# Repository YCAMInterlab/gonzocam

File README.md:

# gonzocam

Open source hardware kit for disposable camera or iPhone to take pictures of wild animals automatically.

gonzocam（ゴンゾカム）は市販のインスタントカメラを使って人間含む野生動物を自動撮影するためのオープンソースハードウェアキットです。インスタントカメラに装着することで、周囲の物体の動きや加速度の変化などをトリガーにシャッターを切り、自動的にフィルムを巻き上げるなどカメラ本来の機能を拡張することができます。

詳しい情報は[YCAM Interlab | gonzocam](http://interlab.ycam.jp/projects/gonzocam)を参照してください。

## Licenses

### Hardware of gonzocam

<br />
<span xmlns:dct="http://purl.org/dc/terms/" property="dct:title">Circuit diagram, Parts list, Gerber format data</span> by <a xmlns:cc="http://creativecommons.org/ns#" href="http://yang02.org/" property="cc:attributionName" rel="cc:attributionURL">yang02</a> is licensed under a <a rel="license" href="http://creativecommons.org/licenses/by-sa/3.0/deed.en_US">Creative Commons Attribution-ShareAlike 3.0 Unported License</a>.

### Software of gonzocam

Arduino sketch by Takahiro Yamaguchi is licensed under the [Apache License, Version2.0](http://www.apache.org/licenses/LICENSE-2.0.html)

    Copyright 2013 Takahiro Yamaguchi

    Licensed under the Apache License, Version 2.0 (the "License");
    you may not use this file except in compliance with the License.
    You may obtain a copy of the License at

       http://www.apache.org/licenses/LICENSE-2.0

    Unless required by applicable law or agreed to in writing, software
    distributed under the License is distributed on an "AS IS" BASIS,
    WITHOUT WARRANTIES OR CONDITIONS OF ANY KIND, either express or implied.
    See the License for the specific language governing permissions and
    limitations under the License.

### Hardware of igonzocam

<br />
<span xmlns:dct="http://purl.org/dc/terms/" property="dct:title">Circuit diagram, Parts list</span> by <a xmlns:cc="http://creativecommons.org/ns#" href="http://www.inafact.net/" property="cc:attributionName" rel="cc:attributionURL">inafact</a> is licensed under a <a rel="license" href="http://creativecommons.org/licenses/by-sa/3.0/deed.en_US">Creative Commons Attribution-ShareAlike 3.0 Unported License</a>.

### Software of igonzocam

iOS software by YCAM InterLab and Takanobu Inafuku are licensed under the [Apache License, Version2.0](http://www.apache.org/licenses/LICENSE-2.0.html)

    Copyright 2013 YCAM InterLab and Takanobu Inafuku

    Licensed under the Apache License, Version 2.0 (the "License");
    you may not use this file except in compliance with the License.
    You may obtain a copy of the License at

       http://www.apache.org/licenses/LICENSE-2.0

    Unless required by applicable law or agreed to in writing, software
    distributed under the License is distributed on an "AS IS" BASIS,
    WITHOUT WARRANTIES OR CONDITIONS OF ANY KIND, either express or implied.
    See the License for the specific language governing permissions and
    limitations under the License.

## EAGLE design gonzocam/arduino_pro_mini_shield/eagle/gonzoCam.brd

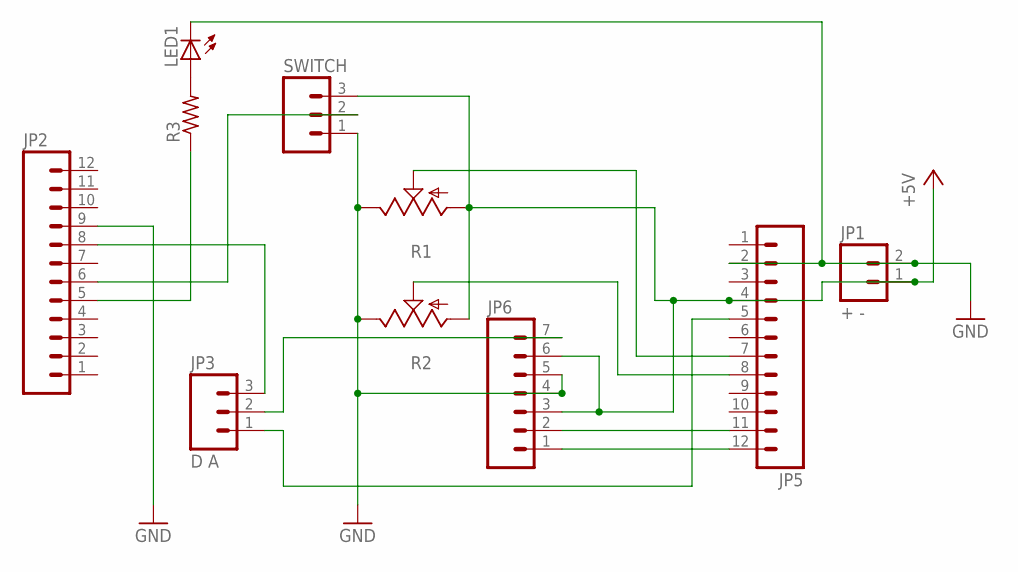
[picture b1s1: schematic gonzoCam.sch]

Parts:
JP1: + -; 1X02
JP2, JP5: M12PTH; 1X12
JP3: D A; 1X03
JP6: M07; 1X07
LED1: LED3MM
R1, R2: TRIM_US-CA6V; CA6V
R3: R-US_0204/5; 0204/5
SWITCH: M03PTH; 1X03

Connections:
+5V: JP1.1, JP5.4, JP6.3, JP6.6, R1.A, R2.A, SWITCH.3
GND: JP1.2, JP2.9, JP5.2, JP6.4, JP6.5, LED1.K (C), R1.E, R2.E, SWITCH.1
unnamed: JP2.6, SWITCH.2
unnamed: JP2.5, R3.1
unnamed: JP5.11, JP6.2
unnamed: JP5.12, JP6.1
unnamed: JP3.2, JP6.7
unnamed: JP5.8, R2.S
unnamed: JP5.7, R1.S
unnamed: LED1.A, R3.2
unnamed: JP2.8, JP3.3
unnamed: JP3.1, JP5.5

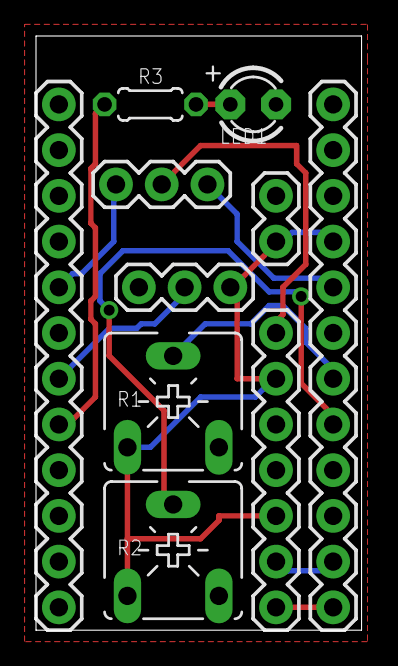
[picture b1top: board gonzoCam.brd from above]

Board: 2 copper layers, 18.1 x 33.0 mm, 10 parts (0 on the bottom side), 12 nets.

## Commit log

2013-09-12 Update README.md
    ダミー文章、ダミー画像、ライセンス文章の追加
2013-09-22 Uploaded .ino code for Arduino
2013-09-22 Uploaded circuits data
2013-09-22 Uploaded parts list
2013-09-23 Uploaded pdf files for camera case
2013-09-23 Fixed pdf data
    gonzocamロゴ入ってなかったので上げなおし
2013-09-27 igonzocam first commit
2013-09-27 added README
2013-09-29 Integrated to audioInUpdate & motionSensoUpdate from some functions, cleanup. fixed #3
2013-09-30 Update LICENSE
2014-01-26 apply license
2014-01-26 Create LICENSE
2014-01-26 add igonzocam hardware

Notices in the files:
README.md:
CC BY-SA 3.0
parts and their libraries:
SparkFun-Connectors: Licensing: CC v3.0 Share-Alike You are welcome to use this library for commercial purposes.
